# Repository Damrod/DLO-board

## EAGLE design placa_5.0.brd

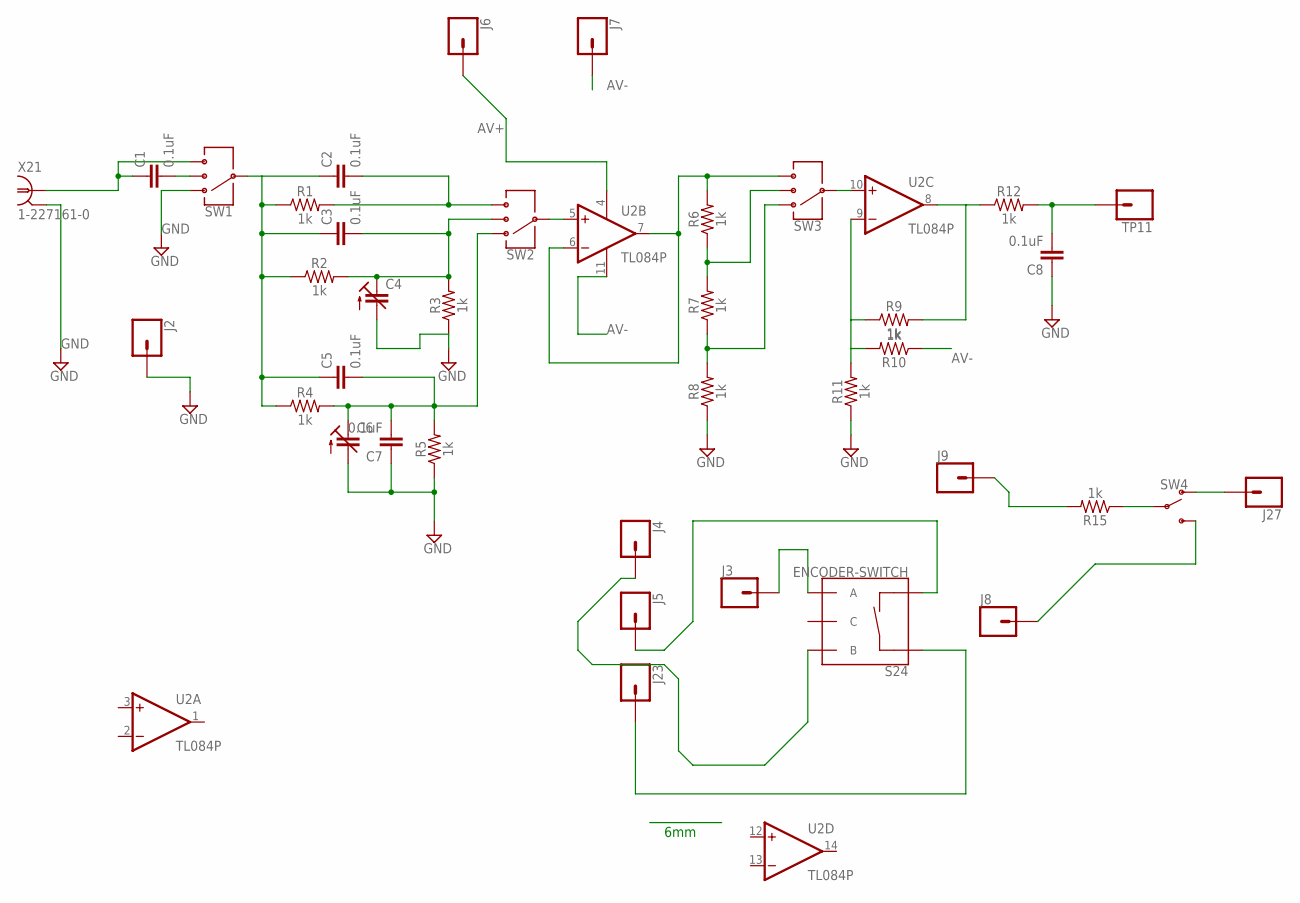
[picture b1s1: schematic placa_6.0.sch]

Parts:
C1, C2, C3, C5, C7, C8: 0.1uF; CAP-PTH-SMALL-KIT
C4, C6: C-TRIMM3050.504; CTRIM3050.504
J2, J3, J4, J5, J6, J7, J8, J9, J23, J27: CONN_01; 1X01
R1, R2, R3, R4, R5, R6, R7, R8, R9, R10, R11, R12, R15: 1k; AXIAL-0.3
S24: ENCODER-SWITCH; ROTARY_ENC_PLAIN
SW1, SW2, SW3: SWITCH-SP3T-SMD; SWITCH_SP3T_SMD
SW4: SWITCH-SPDT-PTH-11.6X4.0MM; SWITCH_SPDT_PTH_11.6X4.0MM
TP11: CONN_01; 1X01
U2: TL084P; DIL14
X21: 1-227161-0; AMP_227161

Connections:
AV+: J6.1, U2.4 (V+)
AV-: J7.1, R10.P$1 (1), U2.11 (V-)
GND: C4.2 (A), C6.2 (A), C7.1, C8.1, J2.1, R3.P$1 (1), R5.P$1 (1), R8.P$1 (1), R11.P$1 (1), SW1.IO1 (1), X21.2
unnamed: C1.1, SW1.IO4 (4), X21.1
unnamed: C1.>NAME (2), SW1.IO2 (2)
unnamed: C2.1, C3.1, C5.1, R1.P$1 (1), R2.P$1 (1), R4.P$1 (1), SW1.IO3 (3)
unnamed: C3.>NAME (2), C4.1 (E), R2.P$2 (2), R3.P$2 (2), SW2.IO2 (2)
unnamed: C2.>NAME (2), R1.P$2 (2), SW2.IO4 (4)
unnamed: C5.>NAME (2), C6.1 (E), C7.>NAME (2), R4.P$2 (2), R5.P$2 (2), SW2.IO1 (1)
unnamed: SW2.IO3 (3), U2.5 (+IN)
unnamed: J9.1, R15.P$2 (2)
unnamed: R6.P$1 (1), R7.P$2 (2), SW3.IO2 (2)
unnamed: R7.P$1 (1), R8.P$2 (2), SW3.IO1 (1)
unnamed: SW3.IO3 (3), U2.10 (+IN)
unnamed: R9.P$1 (1), R10.P$2 (2), R11.P$2 (2), U2.9 (-IN)
unnamed: R15.P$1 (1), SW4.2
unnamed: J8.1, SW4.3 (S)
unnamed: J27.1, SW4.1 (O)
unnamed: C8.>NAME (2), R12.P$2 (2), TP11.1
unnamed: J3.1, S24.A
unnamed: J4.1, S24.B
unnamed: J23.1, S24.SW+
unnamed: J5.1, S24.SW-
V1: R6.P$2 (2), SW3.IO4 (4), U2.6 (-IN), U2.7 (OUT)
V2: R9.P$2 (2), R12.P$1 (1), U2.8 (OUT)

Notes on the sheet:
6mm

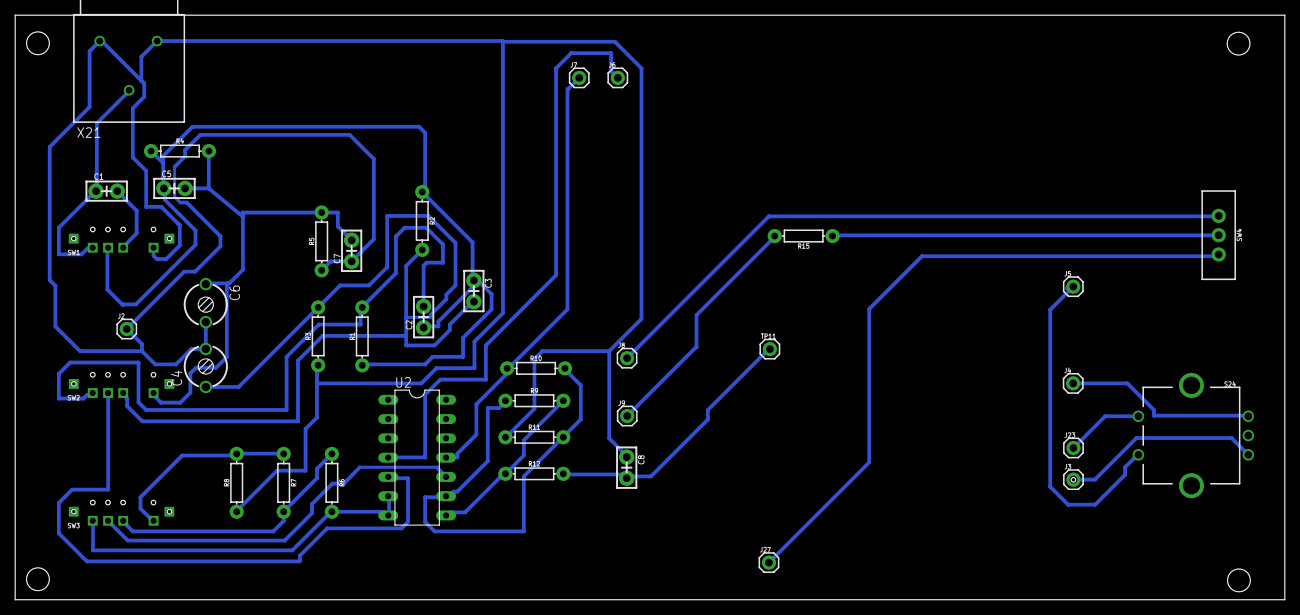
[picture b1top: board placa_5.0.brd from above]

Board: 2 copper layers, 167.2 x 77.0 mm, 39 parts (0 on the bottom side), 25 nets.

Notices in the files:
parts and their libraries:
SparkFun-Capacitors: Licensing: Creative Commons ShareAlike 4.0 International - https://creativecommons.org/licenses/by-sa/4.0
